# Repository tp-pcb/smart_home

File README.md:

# smart_home
Smart home controller based on Atmega8

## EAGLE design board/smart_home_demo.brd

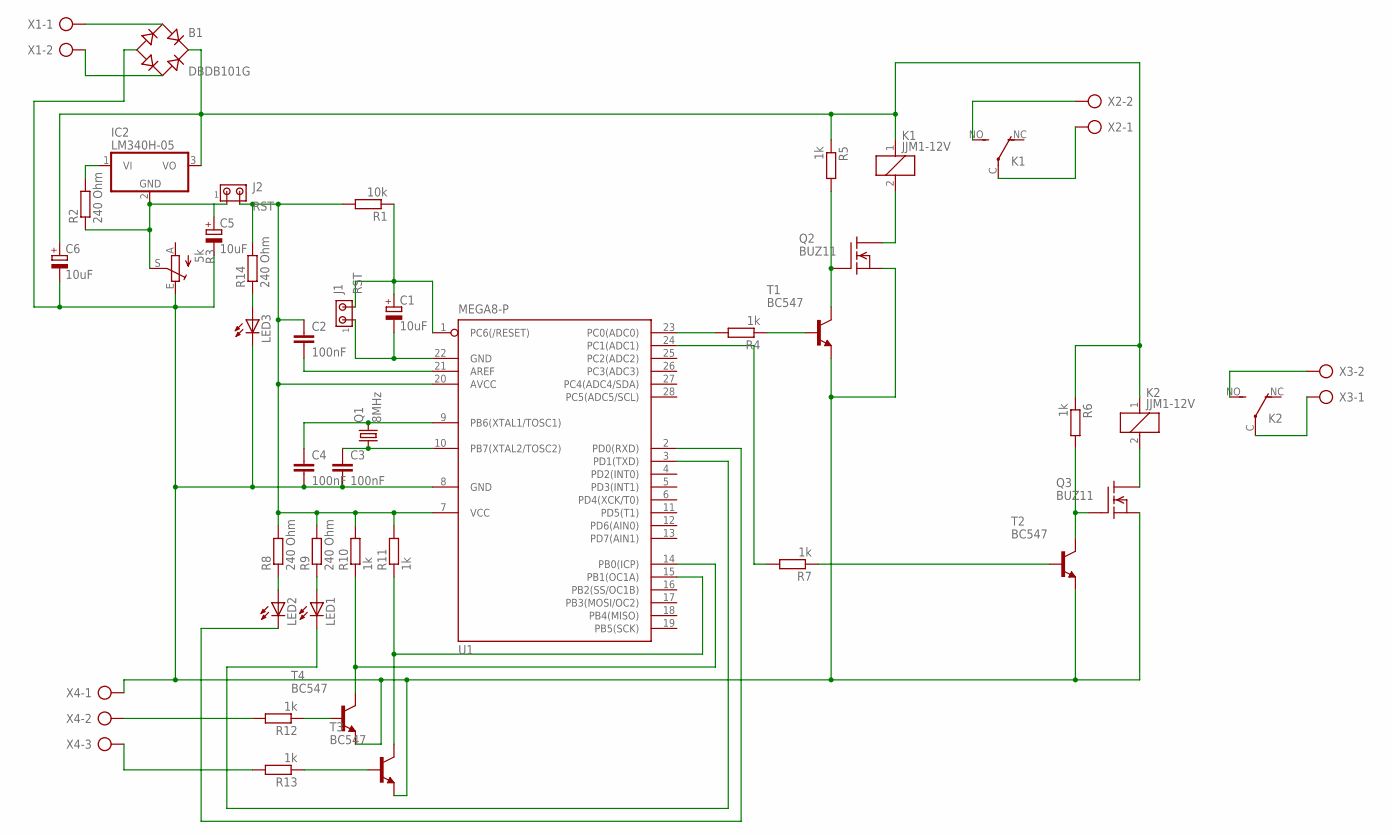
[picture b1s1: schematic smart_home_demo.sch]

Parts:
B1: DBDB101G; DB
C1, C5, C6: 10uF; E2,5-7
C2, C3, C4: 100nF; C1206K
IC2: LM340H-05; TO220H
J1, J2: RST; 10X02MTA
K1, K2: JJM1-12V; JJM1C
LED1, LED2, LED3: LED5MM
Q1: 8MHz; MC-405
Q2, Q3: BUZ11; TO220
R1: 10k; R1206
R2, R8, R9, R14: 240 Ohm; R1206
R3: 5k; CA6V
R4, R5, R6, R7, R10, R11, R12, R13: 1k; R1206
T1, T2, T3, T4: BC547; TO92
U1: MEGA8-P; DIL28-3
X1, X2, X3: AK300/2
X4: AK300/3

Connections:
unnamed: C1.-, J1.1, U1.22 (GND)
unnamed: C1.+, J1.2, R1.1, U1.1 (PC6(/RESET))
unnamed: C2.2, U1.21 (AREF)
unnamed: C2.1, J2.2, R1.2, R8.2, R9.2, R10.2, R11.2, R14.2, U1.7 (VCC), U1.20 (AVCC)
unnamed: B1.-, C3.2, C4.2, C5.-, C6.-, LED3.K (C), Q2.3 (S), Q3.3 (S), R3.E, T1.1 (E), T2.1 (E), T3.1 (E), T4.1 (E), U1.8 (GND), X4.1
unnamed: C4.1, Q1.2, U1.9 (PB6(XTAL1/TOSC1))
unnamed: C3.1, Q1.1, U1.10 (PB7(XTAL2/TOSC2))
unnamed: C5.+, IC2.2 (GND), J2.1, R2.1, R3.S
unnamed: B1.AC1, X1.1
unnamed: B1.AC2, X1.2
unnamed: R7.1, T2.2 (B)
unnamed: IC2.1 (VI), R2.2
unnamed: R4.2, U1.23 (PC0(ADC0))
unnamed: R4.1, T1.2 (B)
unnamed: Q2.1 (G), R5.2, T1.3 (C)
unnamed: B1.+, C6.+, IC2.3 (VO), K1.1, K2.1, R5.1, R6.1
unnamed: K1.2, Q2.2 (D)
unnamed: R7.2, U1.24 (PC1(ADC1))
unnamed: K1.C, X2.1
unnamed: K1.NO (S), X2.2
unnamed: K2.C, X3.1
unnamed: K2.NO (S), X3.2
unnamed: Q3.1 (G), R6.2, T2.3 (C)
unnamed: K2.2, Q3.2 (D)
unnamed: LED2.A, R8.1
unnamed: LED1.A, R9.1
unnamed: R10.1, T4.3 (C), U1.14 (PB0(ICP))
unnamed: R11.1, T3.3 (C), U1.15 (PB1(OC1A))
unnamed: R12.1, T4.2 (B)
unnamed: R13.1, T3.2 (B)
unnamed: R12.2, X4.2
unnamed: R13.2, X4.3
unnamed: LED1.K (C), U1.3 (PD1(TXD))
unnamed: LED2.K (C), U1.2 (PD0(RXD))
unnamed: LED3.A, R14.1

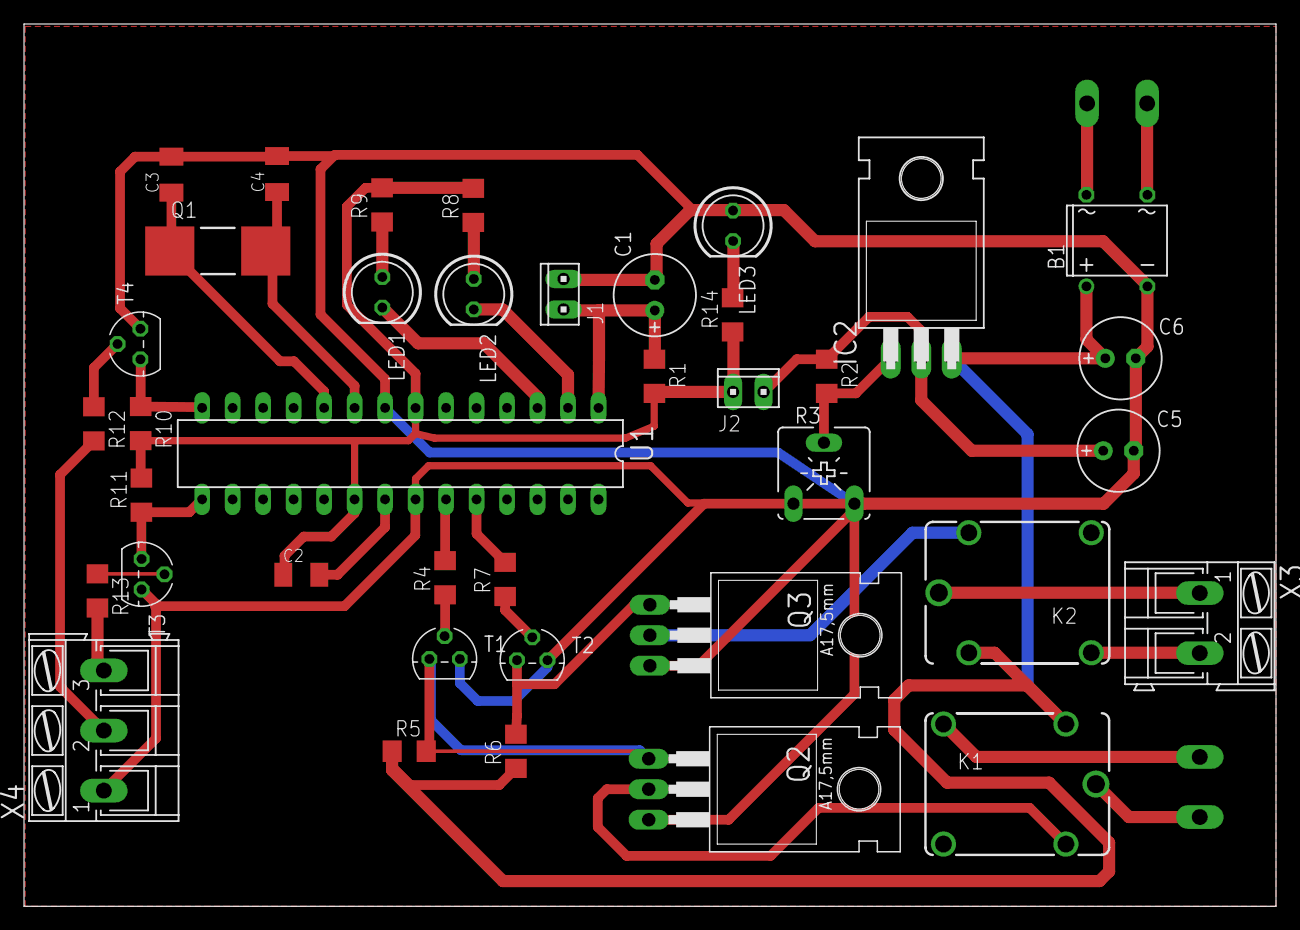
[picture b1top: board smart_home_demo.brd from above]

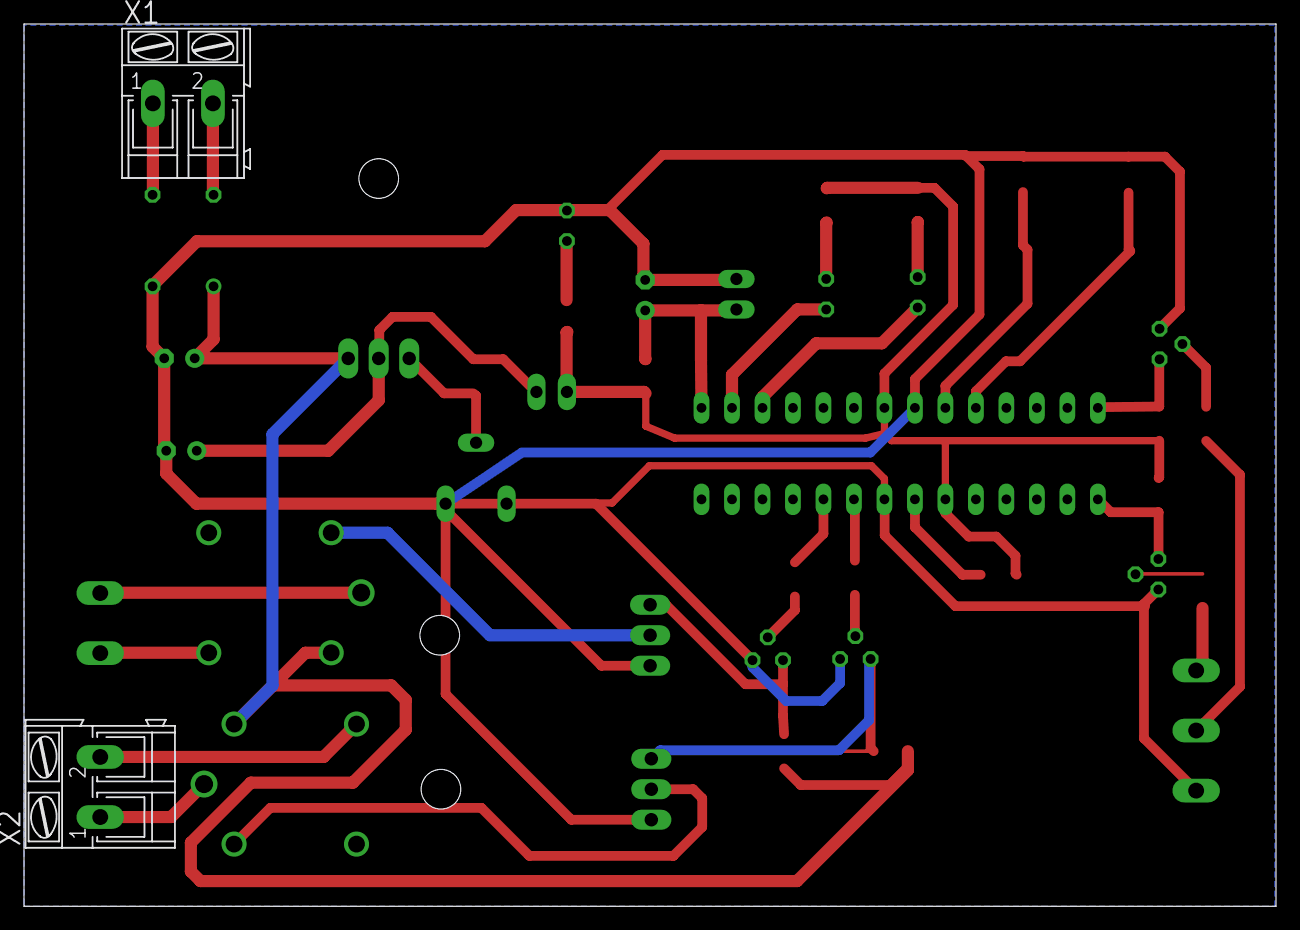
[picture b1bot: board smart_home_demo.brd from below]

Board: 2 copper layers, 104.3 x 73.5 mm, 41 parts (2 on the bottom side), 35 nets.

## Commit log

2023-04-17 designed board
